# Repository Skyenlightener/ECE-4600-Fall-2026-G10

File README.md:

# Campus 3D Reconstruction and Point-Cloud Classification Project

## 1. Project Objective

This project uses aerial photographs and campus point clouds to build a 3D campus environment. An AI model trained in ArcGIS classifies the points in LAS files into roads, low vegetation, trees, and buildings. The classified data can then support GIS analysis, scene separation, and UE5/VR visualization.

This document covers the project up to AI model version 1 (v1).

| Class Code | Class |
|---:|---|
| 0 | Road and other hard-paved surfaces |
| 1 | Low vegetation, including grass |
| 2 | Trees and other tall vegetation |
| 3 | Buildings and designated built objects |

## 2. Main Software and Tools

### ArcGIS Pro

ArcGIS Pro is used to view, edit, and manage LAS point clouds, create manual classification labels, export training data, and train and run the point-cloud classification model. The model predicts a class for each point and writes the result to the LAS `Classification` field.

### ArcGIS Deep Learning Libraries / PyTorch

These libraries provide the deep-learning environment and GPU acceleration required for AI training and inference. The v1 model uses an ArcGIS point-cloud classification network to identify roads, vegetation, trees, and buildings from point positions, surrounding geometry, and RGB colour information.

### Python

Python is used to process LAS data, check manual labels, preserve or restore RGB information, and automate parts of the data-preparation and classification workflow. It supports the ArcGIS training process but does not generate the final VR environment.

### Gaussian Splatting

Gaussian Splatting reconstructs a 3D scene from photographs taken from multiple viewpoints and their camera positions. The scene is represented by many 3D Gaussians containing position, scale, orientation, colour, and opacity information. It is well suited to photorealistic appearance and real-time viewing. Its purpose is to reproduce the visual appearance of the campus, not to classify objects as buildings, roads, or trees.

### Mesh / Photogrammetry Model

A mesh converts photographs, depth information, or point clouds into a 3D surface made of vertices and triangles. Meshes are suitable for collision detection, physical interaction, model editing, and UE5 scene construction. This project combines the stable geometry of a mesh with the realistic appearance of Gaussian Splatting.

### SpeedTree

SpeedTree is used to create and edit trees, shrubs, and other vegetation models. It can generate trunks, branches, leaves, wind animation, and multiple levels of detail (LODs) for export to UE5. SpeedTree assets can replace incomplete trees in point clouds or Gaussian Splatting, producing vegetation that is clearer, lighter, and more suitable for real-time rendering.

### MLSLabsRenderer Interface

The MLSLabsRenderer interface is used to display and manage Gaussian Splatting models in UE5 and to coordinate the rendering relationship between Gaussian and mesh models. When both models occupy similar positions, they may compete for the same pixel depth, causing incorrect occlusion, flickering, or unstable front-to-back relationships. MLSLabsRenderer helps address these depth conflicts so that Gaussian and mesh models can be displayed together more reliably in one UE5 scene.

### Unreal Engine 5 / VR

Unreal Engine 5 is used to combine Gaussian Splatting, meshes, SpeedTree vegetation, materials, lighting, and interactive functions into the final navigable campus VR environment.

## 3. Training Dataset Source

The original point-cloud data used by this project was downloaded from:

**[FE Studio Point Cloud Research](https://festudio.ca/research/pointcloud)**

This website was created by **Professor Yuhao of the University of Manitoba's Department of Architecture** to publish and introduce the related point-cloud research data.

Representative areas were selected from the campus point clouds provided on the website. Their classification labels were then created and corrected manually in ArcGIS Pro. The training samples include buildings, roads, low vegetation, trees, and mixed-class areas. XYZ coordinates and RGB colour information are preserved during data preparation, after which ArcGIS divides and exports the processed LAS data into the point-cloud training format required by the v1 model.

## 4. AI Model v1

The colour point-cloud v1 model used at this stage is located at:

**[FE Studio Point Cloud Research](https://festudio.ca/research/pointcloud)**

The main files are:

- `.emd`: model structure, class definitions, and input information;
- `.pth`: trained PyTorch model weights;
- `.dlpk`: complete model package for use in ArcGIS Pro;
- `model_metrics.html`: training curves and model evaluation information.

The primary inputs to v1 are the XYZ coordinates and RGB colours stored in the LAS files. ArcGIS divides the point cloud into smaller spatial blocks. The model learns the colour, shape, height, and neighbourhood characteristics of each class and then predicts a classification for every point.

## 5. Relationship Between Project Components

```text
Aerial photographs
   ↓
RGB point cloud / LAS Manual
   ↓
ArcGIS labels and AI v1 classification
   ↓
Classification results, mesh, Gaussian model, and SpeedTree vegetation
   ↓
Gaussian Splatting and mesh reconstruction
   ↓
MLSLabsRenderer depth coordination
   ↓
UE5 / VR campus environment
```

Gaussian Splatting and meshes describe what the campus looks like. The ArcGIS AI identifies what the individual point-cloud points represent. SpeedTree creates vegetation suitable for real-time rendering, while MLSLabsRenderer coordinates the display and depth relationship between Gaussian and mesh models in UE5.

Original LAS files, manual labels, AI outputs, and 3D models should be stored separately. Original data should never be overwritten.

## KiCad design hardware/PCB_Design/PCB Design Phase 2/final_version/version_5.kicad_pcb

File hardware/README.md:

# Hardware

This folder contain everything regarding the hardware design in our capstone project

- PCB design
  - schematics
  - layout
- Analog to Digital Signal Conversion
- Digital Signal Processing
  - Result Visualization
  - Result Analyses

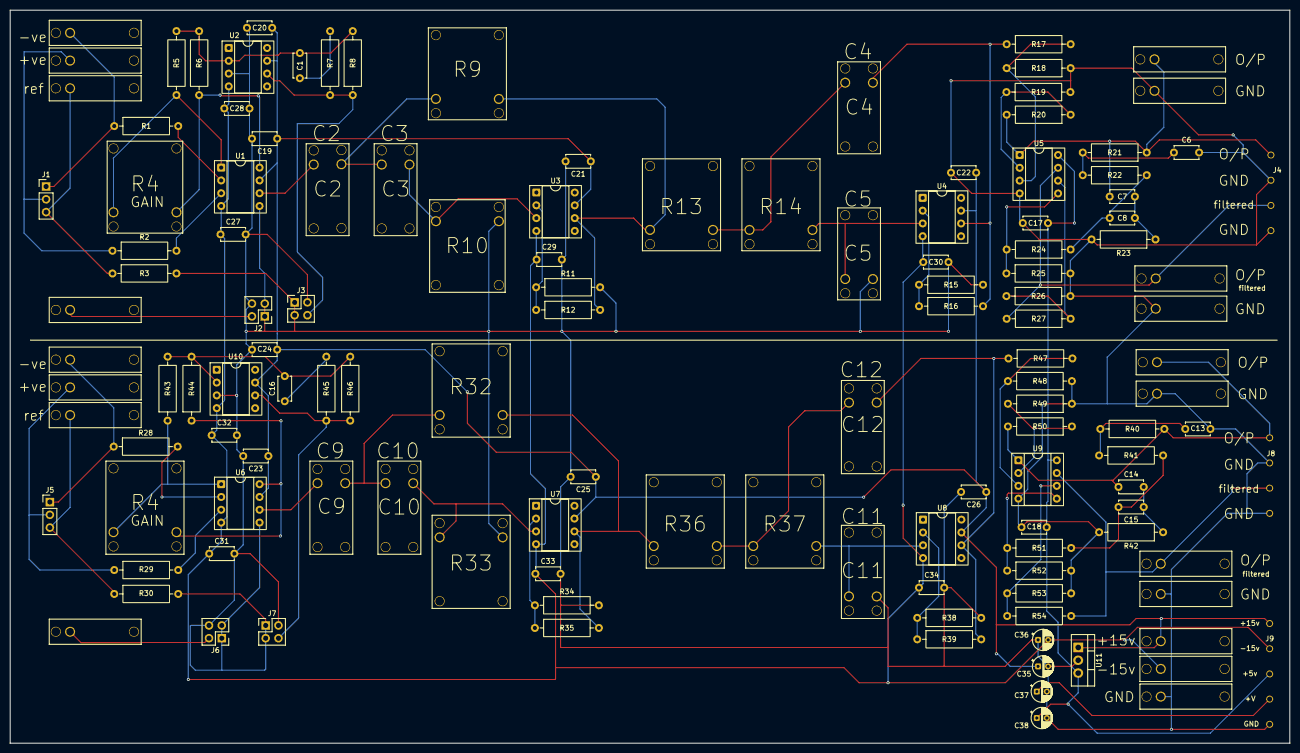
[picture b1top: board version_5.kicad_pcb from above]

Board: 2 copper layers, 254.0 x 145.5 mm, 149 parts (0 on the bottom side), 63 nets.

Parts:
C1, C16, C17, C18, C19, C20, C21, C22, C23, C24, C25, C26, C27, C28, C29, C30, C31, C32, C33, C34: 100nF; C_Disc_D4.7mm_W2.5mm_P5.00mm
C6, C13: 6.8nF; C_Disc_D4.7mm_W2.5mm_P5.00mm
C7, C8, C14, C15: 1nF; C_Disc_D4.7mm_W2.5mm_P5.00mm
C35, C36, C37, C38: 100uF; CP_Radial_D4.0mm_P2.00mm
J1, J5: ELECTRODE_HEADER; PinHeader_1x03_P2.54mm_Vertical
J2, J3, J6, J7: REF_SELECT_DNP; PinHeader_2x02_P2.54mm_Vertical
J4, J8: OUTPUT_HEADER_DNP; 1x04 TH header 5.00mm
J9: POWER_EXPANSION_DNP; 1x05 TH header 5.00mm
R1, R2, R11, R12, R15, R16, R17, R18, R19, R20, R24, R25, R26, R27, R28, R29, R34, R35, R38, R39, R47, R48, R49, R50, R51, R52, R53, R54: 220k; R_Axial_DIN0309_L9.0mm_D3.2mm_P12.70mm_Horizontal
R3, R30: 10; R_Axial_DIN0309_L9.0mm_D3.2mm_P12.70mm_Horizontal
R5, R6, R7, R43, R44, R45: 10k; R_Axial_DIN0309_L9.0mm_D3.2mm_P12.70mm_Horizontal
R8, R46: 1Meg; R_Axial_DIN0309_L9.0mm_D3.2mm_P12.70mm_Horizontal
R21, R22, R40, R41: 1.5Meg; R_Axial_DIN0309_L9.0mm_D3.2mm_P12.70mm_Horizontal
R23, R42: 2.7Meg; R_Axial_DIN0309_L9.0mm_D3.2mm_P12.70mm_Horizontal
T8, T16: Socket_5Hole_Common
U1, U6: AD620AN; DIP-8_W7.62mm_Socket
U2, U3, U4, U7, U8, U10: LF351N; DIP-8_W7.62mm_Socket
U5, U9: OPA2337PA; DIP-8_W7.62mm_Socket
U11: LM7805CT; TO-220-3_Vertical
XS101, XS102, XS103, XS104, XS105, XS106, XS107, XS108, XS109, XS110, XS111, XS112, XS113, XS114, XS115, XS116, XS117, XS118, XS119, XS120, XS121, XS122, XS123, XS124, XS125, XS201, XS202, XS203, XS204, XS205, XS206, XS207, XS208, XS209, XS210, XS211, XS212, XS213, XS214, XS215, XS216, XS217, XS218, XS219, XS220, XS221, XS222, XS223, XS224, XS225, XS301, XS302, XS303: Socket_5Hole_Common

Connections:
+5V: C17.1, C18.1, C38.1, J9.3, U5.8 (V+), U9.8 (V+), U11.3 (VO)
+15V: C19.1, C20.1, C21.1, C22.1, C23.1, C24.1, C25.1, C26.1, C35.1, J9.1, U1.7 (Vs+), U2.7 (V+), U3.7 (V+), U4.7 (V+), U6.7 (Vs+), U7.7 (V+), U8.7 (V+), U10.7 (V+), U11.1 (VI), XS301.1 (COMMON_1)
-15V: C27.1, C28.1, C29.1, C30.1, C31.1, C32.1, C33.1, C34.1, C36.2, J9.2, U1.4 (Vs-), U2.4 (V-), U3.4 (V-), U4.4 (V-), U6.4 (Vs-), U7.4 (V-), U8.4 (V-), U10.4 (V-), XS302.1 (COMMON_1)
/+V_AUX: C37.1, J9.4
/CH1 Reference Replica/CH1_DRL_COMP: C1.1, R7.2
/CH1 Reference Replica/CH1_DRL_OUT: J3.4, R7.1, R8.1, U2.6
/CH1 Reference Replica/CH1_DRL_SUM: C1.2, R5.2, R6.2, R8.2, U2.2 (-)
/CH1 Reference Replica/CH1_ELECTRODE_REF: J1.3, R3.1, XS121.1 (COMMON_1)
/CH1 Reference Replica/CH1_EXT_REF: J2.2, T8.1 (COMMON_1)
/CH1 Reference Replica/CH1_HP_N1: XS104.1 (COMMON_1), XS105.1 (COMMON_1), XS107.1 (COMMON_1)
/CH1 Reference Replica/CH1_HP_OUT: R12.2, U3.6, XS108.1 (COMMON_1), XS111.1 (COMMON_1)
/CH1 Reference Replica/CH1_HP_PLUS: U3.3 (+), XS106.1 (COMMON_1), XS109.1 (COMMON_1)
/CH1 Reference Replica/CH1_IA_OUT: U1.6, XS103.1 (COMMON_1)
/CH1 Reference Replica/CH1_IN_MINUS: J1.1, R1.1, XS119.1 (COMMON_1)
/CH1 Reference Replica/CH1_IN_PLUS: J1.2, R2.1, XS120.1 (COMMON_1)
/CH1 Reference Replica/CH1_LP_N1: XS112.1 (COMMON_1), XS113.1 (COMMON_1), XS115.1 (COMMON_1)
/CH1 Reference Replica/CH1_LP_OUT: R16.2, R17.1, U4.6, XS116.1 (COMMON_1)
/CH1 Reference Replica/CH1_LP_PLUS: U4.3 (+), XS114.1 (COMMON_1), XS117.1 (COMMON_1)
/CH1 Reference Replica/CH1_RG_A: R5.1, U1.1 (Rg), XS101.1 (COMMON_1)
/CH1 Reference Replica/CH1_RG_B: R6.1, U1.8 (Rg), XS102.1 (COMMON_1)
/CH1_BYPASS: C7.1, J4.1, R20.2, R21.1, U5.1, XS122.1 (COMMON_1)
/CH1_FILTERED: J4.3, R27.2, U5.7, XS124.1 (COMMON_1)
/CH2 Reference Replica/CH2_DRL_COMP: C16.1, R45.2
/CH2 Reference Replica/CH2_DRL_OUT: J7.4, R45.1, R46.1, U10.6
/CH2 Reference Replica/CH2_DRL_SUM: C16.2, R43.2, R44.2, R46.2, U10.2 (-)
/CH2 Reference Replica/CH2_ELECTRODE_REF: J5.3, R30.1, XS221.1 (COMMON_1)
/CH2 Reference Replica/CH2_EXT_REF: J6.2, T16.1 (COMMON_1)
/CH2 Reference Replica/CH2_HP_N1: XS204.1 (COMMON_1), XS205.1 (COMMON_1), XS207.1 (COMMON_1)
/CH2 Reference Replica/CH2_HP_OUT: R35.2, U7.6, XS208.1 (COMMON_1), XS211.1 (COMMON_1)
/CH2 Reference Replica/CH2_HP_PLUS: U7.3 (+), XS206.1 (COMMON_1), XS209.1 (COMMON_1)
/CH2 Reference Replica/CH2_IA_OUT: U6.6, XS203.1 (COMMON_1)
/CH2 Reference Replica/CH2_IN_MINUS: J5.1, R28.1, XS219.1 (COMMON_1)
/CH2 Reference Replica/CH2_IN_PLUS: J5.2, R29.1, XS220.1 (COMMON_1)
/CH2 Reference Replica/CH2_LP_N1: XS212.1 (COMMON_1), XS213.1 (COMMON_1), XS215.1 (COMMON_1)
/CH2 Reference Replica/CH2_LP_OUT: R39.2, R47.1, U8.6, XS216.1 (COMMON_1)
/CH2 Reference Replica/CH2_LP_PLUS: U8.3 (+), XS214.1 (COMMON_1), XS217.1 (COMMON_1)
/CH2 Reference Replica/CH2_RG_A: R43.1, U6.1 (Rg), XS201.1 (COMMON_1)
/CH2 Reference Replica/CH2_RG_B: R44.1, U6.8 (Rg), XS202.1 (COMMON_1)
/CH2_BYPASS: C14.1, J8.1, R40.1, R50.2, U9.1, XS222.1 (COMMON_1)
/CH2_FILTERED: J8.3, R54.2, U9.7, XS224.1 (COMMON_1)
GND: C6.2, C13.2, C17.2, C18.2, C19.2, C20.2, C21.2, C22.2, C23.2, C24.2, C25.2, C26.2, C27.2, C28.2, C29.2, C30.2, C31.2, C32.2, C33.2, C34.2, C35.2, C36.1, C37.2, C38.2, J2.1, J2.3, J2.4, J3.1, J3.2, J3.3, J4.2, J4.4, J6.1, J6.3, J6.4, J7.1, J7.2, J7.3, J8.2, J8.4, J9.5, R3.2, R11.2, R15.2, R18.1, R19.1, R23.2, R25.2, R26.2, R30.2, R34.2, R38.2, R42.2, R48.1, R49.1, R52.2, R53.2, U1.5 (Ref), U2.3 (+), U5.4 (V-), U6.5 (Ref), U9.4 (V-), U10.3 (+), U11.2 (GND), XS110.1 (COMMON_1), XS118.1 (COMMON_1), XS123.1 (COMMON_1), XS125.1 (COMMON_1), XS210.1 (COMMON_1), XS218.1 (COMMON_1), XS223.1 (COMMON_1), XS225.1 (COMMON_1), XS303.1 (COMMON_1)
unnamed: C6.1, R21.2, R22.1
unnamed: C7.2, C8.1, R23.1
unnamed: C8.2, R22.2, R24.1
unnamed: C13.1, R40.2, R41.1
unnamed: C14.2, C15.1, R42.1
unnamed: C15.2, R41.2, R51.1
unnamed: R2.2, U1.3 (+)
unnamed: R1.2, U1.2 (-)
unnamed: R11.1, R12.1, U3.2 (-)
unnamed: R15.1, R16.1, U4.2 (-)
unnamed: R17.2, R18.2, U5.3 (+)
unnamed: R19.2, R20.1, U5.2 (-)
unnamed: R24.2, R25.1, U5.5 (+)
unnamed: R26.1, R27.1, U5.6 (-)
unnamed: R29.2, U6.3 (+)
unnamed: R28.2, U6.2 (-)
unnamed: R34.1, R35.1, U7.2 (-)
unnamed: R38.1, R39.1, U8.2 (-)
unnamed: R47.2, R48.2, U9.3 (+)
unnamed: R49.2, R50.1, U9.2 (-)
unnamed: R51.2, R52.1, U9.5 (+)
unnamed: R53.1, R54.1, U9.6 (-)
